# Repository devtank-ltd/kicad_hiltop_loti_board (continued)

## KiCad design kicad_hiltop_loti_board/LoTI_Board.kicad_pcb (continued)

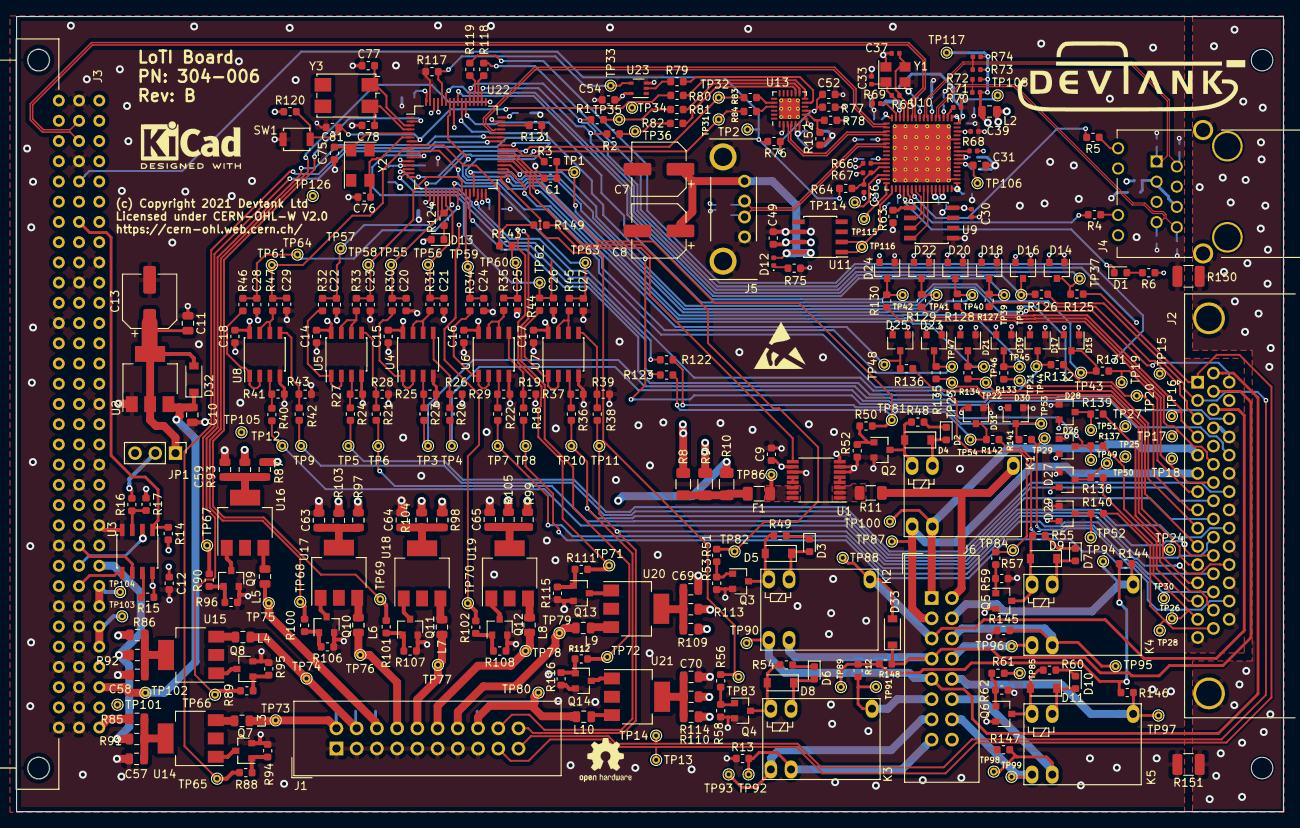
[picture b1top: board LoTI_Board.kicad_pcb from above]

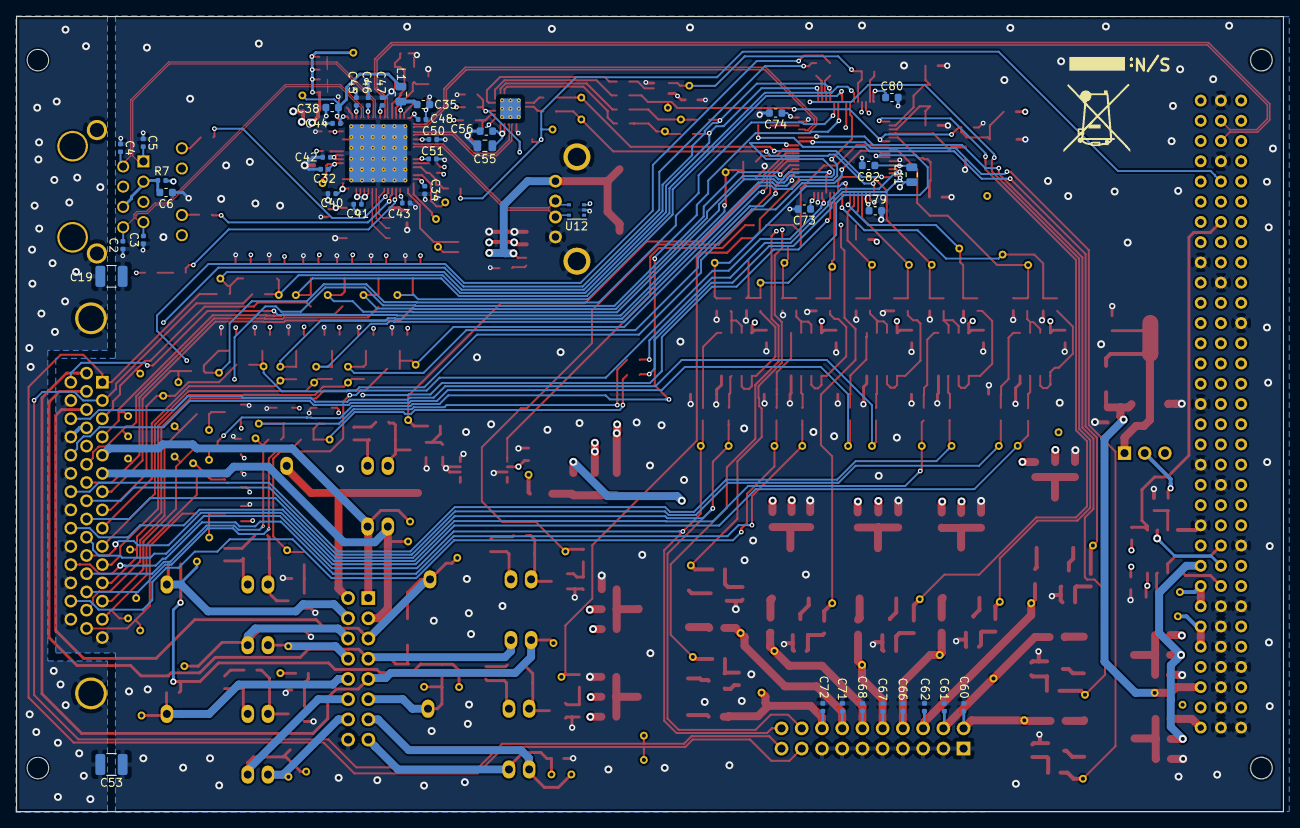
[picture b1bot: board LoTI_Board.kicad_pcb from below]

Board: 4 copper layers, 159.1 x 99.9 mm, 443 parts (41 on the bottom side), 251 nets.

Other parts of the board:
TP117: Test_Point; TestPoint_THTPad_D1.0mm_Drill0.5mm

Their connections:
+3V3_A: TP117.1; also elsewhere on the board

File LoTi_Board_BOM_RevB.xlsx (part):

Title | LoTi Board
Revision | Rev B
Date | 43868
Generated
Company | Devtank Ltd
Comment 1
Comment 2
Comment 3
Comment 4
Total Parts | 439
Total Unique Parts | 74
Ref | Qty | Value | Footprint | Devtank | Description | Manufacturer | Manufacturer Part Number | Supplier | Supplier Part number | Cost (unit) | Cost (total) | Qty (12off) | Cost (12off boards)
C9 C12 C1 C20 C21 C22 C23 C24 C25 C14 C15 C16 C26 C27 C28 C17 C18 C29 C38 C56 C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 | 26 | 100nF | Capacitor_SMD:C_0603_1608Metric | 105-002 | 100nF 50V X7R | Kemet | C0603C104M5RACTU | Farnell | 2581046 | 0.0297 | 0.7722 | 312 | 9.2664
C8 C7 C13 | 3 | 100uF | Capacitor_SMD:CP_Elec_6.3x7.7 | 108-003 | 100uF 50V 0.34R FT Series | Panasonic | EEEFTH101XAP | Farnell | 1868426 | 0.459 | 1.377 | 36 | 16.524
C6 | 1 | 22nF | Resistor_SMD:R_0603_1608Metric | 105-024 | 22nF 16V X7R | AVX | 0603YC223KAT2A | Farnell | 2332669 | 0.146 | 0.146 | 12 | 1.752
C2 C3 C4 C5 | 4 | 15pF | Capacitor_SMD:C_0402_1005Metric | 106-013 | 15pF COG/NPO | AVX | 04025A150JAT2A | Farnell | 1327631 | 0.113 | 0.452 | 48 | 5.424
C10 C11 | 2 | 10uF | Capacitor_SMD:C_0805_2012Metric | 105-001 | 10uF 16V X5R 10% MLCC | AVX | 0805YD106KAT2A | Farnell | 1658880 | 0.148 | 0.296 | 24 | 3.552
C19 C53 | 2 | 100nF | Resistor_SMD:R_1210_3225Metric | 105-020 | 100nF 50V X7R | AVX | 12101C104KAT2A | Farnell | 1327731 | 0.28 | 0.56 | 24 | 6.72
C31 | 1 | 4.7uF | Capacitor_SMD:C_0603_1608Metric | 105-021 | 4.7uF 16V X5R | muRata | GRM188R61C475KAAJD | Farnell | 2611924 | 0.255 | 0.255 | 12 | 3.06
C32 C34 C39 C40 C41 C42 C43 C46 C44 C45 C47 C48 C50 C51 C30 C60 C61 C62 C66 C67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 | 23 | 100nF | Capacitor_SMD:C_0402_1005Metric | 105-019 | 100nF 50V X7R | TDK | C1005X7R1H104M050BB | Farnell | 2525048 | 0.0744 | 1.7112 | 276 | 20.5344
C35 C49 | 2 | 1uF | Capacitor_SMD:C_0603_1608Metric | 105-014 | 1uF 16V X7R | Walsin | 0603B105K160CT | Farnell | 2496835 | 0.298 | 0.596 | 24 | 7.152
C33 C37 | 2 | 18pF | Capacitor_SMD:C_0402_1005Metric | 106-010 | 18pF COG/NPO | AVX | 04025A180JAT2A | Farnell | 1740572 | 0.133 | 0.266 | 24 | 3.192
C36 | 1 | 10nF | Capacitor_SMD:C_0402_1005Metric | 105-017 | 10nF 50V X7R | AVX | 04025C103KAT2A | Farnell | 2332514 | 0.0411 | 0.0411 | 12 | 0.4932
C55 | 1 | 4.7uF | Capacitor_SMD:C_0805_2012Metric | 105-007 | 4.7uF 16V X7R | muRata | GCJ21BR71C475KA01L | Farnell | 2781412 | 0.475 | 0.475 | 12 | 5.7
C52 | 1 | DNF | Capacitor_SMD:C_0603_1608Metric |  |  |  |  |  |  |  | 0 | 12 | 0
C57 C58 C59 C63 C64 C65 C69 C70 | 8 | DNP | Capacitor_SMD:C_0805_2012Metric |  |  |  |  |  |  |  | 0 | 96 | 0
C77 C78 | 2 | 4.3pF | Capacitor_SMD:C_0603_1608Metric | 106-014 | 4.3pF COG/NPO | Kemet | CBR06C439B5GAC | Farnell | 2809587 | 0.0936 | 0.1872 | 24 | 2.2464
C75 C76 | 2 | 18pF | Capacitor_SMD:C_0603_1608Metric | 106-003 | 18pF COG/NPO | AVX | 06035A180JAT2A | Farnell | 1612182 | 0.0668 | 0.1336 | 24 | 1.6032
D1 D2 D3 D6 D7 D10 D13 | 7 | GRN | LED_SMD:LED_0603_1608Metric | 110-002 | Green LED | Rohm Semiconductor | SML-D12P8WT86C | Farnell | 2687486 | 0.075 | 0.525 | 84 | 6.3
D32 | 1 | MBR230LSFT1G | Diode_SMD:D_SOD-123 | 133-006 | Schottky Rectifier, 30 V, 2 A, Single, SOD-123FL | ON Semi | MBR230LSFT1G | Farnell | 2317422 | 0.26 | 0.26 | 12 | 3.12
D33 | 1 | BAT42W | Diode_SMD:D_SOD-123 |  | DNF
D4 D5 D8 D9 D11 | 5 | BAT54T1G | Diode_SMD:D_SOD-123 | 133-007 | BAT54T1G Small Signal Schottky Diode, Single, 30V, 200mA | ON Semi | BAT54T1G | Farnell | 1651157 | 0.183 | 0.915 | 60 | 10.98
D12 | 1 | RED | LED_SMD:LED_0402_1005Metric | 110-005 | LED RED CLEAR 0402 SMD | Rohm Semiconductor | SML-P12VTT86R | Digikey | 846-1168-6-ND | 0.4 | 0.4 | 12 | 4.8
D18 D16 D14 D20 D22 D24 D19 D17 D15 D21 D23 D25 D28 D27 D26 D29 D30 D31 | 18 | BAV99 | Package_TO_SOT_SMD:SOT-23 | 134-001 | BAV99 - Small Signal Diode, Dual Series, 75 V, 300 mA, 1.25 V, 4 ns, 4.5 | Diodes Inc | BAV99 | Farnell | 1902422 | 0.086 | 1.548 | 216 | 18.576
F1 | 1 | Polyfuse | Resistor_SMD:R_1206_3216Metric | 190-003 | PPTC Resettable Fuse, SMD, POLYFUSE 1206L | Littlefuse | 1206L075THYR | Farnell | 1822204 | 0.318 | 0.318 | 12 | 3.816
J3 | 1 | Conn_03x32_DIN41612 | Devtank_PCB_Lib:Socket_DIN41612-CaseC1-full-Male-96Pin-3rows_correct | 717-002 | 406AF-96-MSR-AAE4 (Cards) | Valcon | 406AF-96-MSR-AAE4 | Toby | 406AF-96-MSR-AAE4 | 1.54 | 1.54 | 12 | 18.48
J4 | 1 | RJ45-TRANS_VALCON | Devtank_PCB_Lib:RJ45_TRANSFO_VALCON | 704-001 | RJ45 Ethernet with Magnetics + LEDs 10/100 | Valcon | VSIMJL-88-CC-GY | Toby | VSIMJL-88-CC-GY | 2.19 | 2.19 | 12 | 26.28
J5 | 1 | USB_A | Devtank_PCB_Lib:USB_A_Vertical_Lumberg_2410_01 | 703-003 | USB Type A – PCB vertical | Lumberg | 2410 01 | Toby | 2410-01 | 0.48 | 0.48 | 12 | 5.76
J1 | 1 | Conn_02x10_Odd_Even | Connector_IDC:IDC-Header_2x10_P2.54mm_Vertical | 710-018 | 20 Way Header (Box) |  | 302-S-20-D1R1 | Toby | 302-S-20-D1R1 | 0.14 | 0.14 | 12 | 1.68
J2 | 1 | DB44_MALE_MountingHoles | Connector_Dsub:DSUB-44-HD_Female_Horizontal_P2.29x1.98mm_EdgePinOffset8.35mm_Ho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 | 707-003 | L17HTHBS4F1C - D Sub Connector, HD44, 44 Contacts, Receptacle, Through Hole, DB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 | Amphenol | L17HTHBS4F1C | Farnell | 2401273 | 2.39 | 2.39 | 12 | 28.68
J6 | 1 | Conn_02x08_Odd_Even | Connector_IDC:IDC-Header_2x08_P2.54mm_Vertical | 710-017 | 16 Way Header (Box) |  | 302-S-16-D1R1 | Toby | 302-S-16-D1R1 | 0.12 | 0.12 | 12 | 1.44
JP1 | 1 | Jumper_NC_Dual | Connector_PinHeader_2.54mm:PinHeader_1x03_P2.54mm_Vertical | 710-015 | 3 Way Header (shroudless) | Valcon | THS-03-R | Toby | THS-03-R | 0.04 | 0.04 | 12 | 0.48
K1 K2 K3 K4 K5 | 5 | HRS1KH-S | Devtank_PCB_Lib:Relay_SPDT_HRS1KH-S | 141-002 | Signal Relay 5VDC SPDT 24V 3A HRS1K Series | Multicomp | HRS1KH-S DC5V | Farnell | 9480293 | 0.684 | 3.42 | 60 | 41.04
L1 L2 L3 L4 L5 L6 L7 L8 L9 L10 L11 | 11 | 2A/0.05DCR | Inductor_SMD:L_0805_2012Metric | 113-002 | Ferrite 220 ohm, 2 A, WE-CBF Series, 0.05 ohm, ± 25% | Wurth Elektronik | 742792022 | Farnell | 1635733 | 0.169 | 1.859 | 132 | 22.308
Q2 Q3 Q4 Q5 Q6 Q7 Q8 Q9 Q10 Q11 Q12 Q13 Q14 | 13 | ZXMN6A07F | Package_TO_SOT_SMD:SOT-23 | 170-002 | ZXMN6A07F N Channel 1A, 60V, 0.4Ohm | Diodes Inc | ZXMN6A07FTA | Farnell | 9525769 | 0.397 | 5.161 | 156 | 61.932
R4 R5 R6 R23 R20 R24 R21 R22 R75 R81 R82 R124 | 12 | 330R | Resistor_SMD:R_0603_1608Metric | 101-024 | 330R 1% 0603 | Vishay | CRCW0603330RFKEA | Farnell | 1469803 | 0.0243 | 0.2916 | 144 | 3.4992
R7 | 1 | 10R | Resistor_SMD:R_0402_1005Metric | 101-511 | 10R 1% 0402 | Vishay | CRCW040210R0FKED | Farnell | 1652742 | 0.0147 | 0.0147 | 12 | 0.1764
R16 R15 | 2 | 4K7 | Resistor_SMD:R_0603_1608Metric | 101-009 | 4K7 1% 50V 0603 | Vishay | CRCW06034K70FKEA | Farnell | 121-9062 | 0.0146 | 0.0292 | 24 | 0.3504
R17 R1 R2 R143 R147 R25 R26 R27 R29 R28 R64 R77 R9 R8 | 14 | DNF | Resistor_SMD:R_0603_1608Metric |  |  |  |  |  |  |  | 0 | 168 | 0
R14 R18 R36 R38 R40 R42 R52 R53 R58 R59 R62 R63 R120 | 13 | 10K | Resistor_SMD:R_0603_1608Metric | 101-010 | 10K 1% 0603 | Vishay | CRCW060310K0FKEA | Farnell | 1469748 | 0.0146 | 0.1898 | 156 | 2.2776
R10 R11 | 4 | 0R | Resistor_SMD:R_1206_3216Metric | 101-007 | 0R 1% 1206 | Vishay | CRCW12060000Z0EA | Farnell | 1469963 | 0.0272 | 0.1088 | 48 | 1.3056
R3 R30 R31 R32 R33 R34 R35 R44 R45 R46 R47 | 11 | 100R | Resistor_SMD:R_0603_1608Metric | 101-018 | 100R 1% 50V 100mW CR Series | Bourns Inc | CR0603-FX-1000ELF | Farnell | 2008332 | 0.02 | 0.22 | 132 | 2.64
R13 | 1 | DNF | Resistor_SMD:R_0603_1608Metric |  | DNF | Vishay | CRCW06032K70FKEA | Farnell | 1469768 | 0.0147 | 0.0147 | 12 | 0.1764
R145 | 1 | DNF | Resistor_SMD:R_0603_1608Metric |  | DNF
R149 R83 R84 R76 R122 R123 R118 R119 R121 R80 R79 | 11 | 0R | Resistor_SMD:R_0603_1608Metric | 101-005 | 0R 1% 0603 | Vishay | CRCW06030000Z0EA | Farnell | 1469739 | 0.0193 | 0.2123 | 132 | 2.5476
R78 | 1 | 24K | Resistor_SMD:R_0603_1608Metric | 101-055 | 24K 1% 0603 | Multicomp Pro | MCWR06X2402FTL | Farnell | 2447308 | 0.0034 | 0.0034 | 12 | 0.0408
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
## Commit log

2019-06-06 setup new project git history for Loti board
2019-07-02 Change pathing of common to be relative.
2019-07-02 Put project under Cern ohl version 1.2 license.
2019-07-02 Add missing gitignore.
2019-07-02 Project checkin.
2019-07-03 housekeeping documents
2019-07-03 updated drawing templates
2020-09-14 Rev A
2021-04-09 Rev B updates
